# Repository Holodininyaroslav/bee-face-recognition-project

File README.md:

# Bee Face Recognition Project

> **Security update (2026-09-05):** restart/update local installations; replace previously downloaded installers. Read [SECURITY.md](SECURITY.md) for protected APIs, migration instructions and limitations.

Bee Face Recognition Project is an AI-assisted engineering prototype by **Yaroslav Kholodinin**, a student at **Shenkar College, Israel**. Its primary implementation is native face recognition in **C++ and CUDA** using YuNet detection, SFace embeddings, and a project-owned CUDA similarity kernel.

The project combines a local face-recognition pipeline, an AI MIPS Hive interface, bee / board / mechanics simulations, partial SystemVerilog AI MIPS hardware sources, and several research-concept modules for future swarm communication.

It is not a commercial production service. It is a portfolio and course-style system integration project: the value is in connecting neural inference, GPU/CPU execution, local simulation tools, hardware-oriented MIPS work, browser UI, installers, and a safer browser-to-local-app bridge into one demonstrable environment.

## Live Links

- GitHub Pages portal:  
  https://holodininyaroslav.github.io/bee-face-recognition-project/
- Repository:  
  https://github.com/Holodininyaroslav/bee-face-recognition-project
- Full local suite installer:  
  https://github.com/Holodininyaroslav/bee-face-recognition-project/releases/latest/download/bee_face_full_local_suite_installer.zip
- Optional Colab notebook:  
  https://colab.research.google.com/github/Holodininyaroslav/bee-face-recognition-project/blob/main/colab/colab_public_one_image_site.ipynb
- Native CUDA face-recognition source:
  https://github.com/Holodininyaroslav/bee-face-recognition-project/tree/main/source/native_face_cuda

## Primary Native C++ / CUDA Implementation

Face recognition is the main CUDA workflow in this repository. The native worker decodes and prepares an image in C++, detects and aligns the face with YuNet, generates a 128-dimensional SFace embedding through the CUDA execution path, and compares it with stored reference embeddings using the explicit `sface_cuda.cu` kernel. A sequential native CPU path provides the correctness and performance baseline.

The GitHub Pages portal presents this recognition pipeline first and exposes its exact active C++/CUDA source in seven inspectable stages. The surrounding Hive, bee-simulation, hardware, and communication modules remain integrations around this central recognition engine.

## What Works Now

The current project package is built around the local Hive service.

- Local face recognition through the Hive service.
- Local CPU recognition path.
- Local OpenCL recognition path for AMD/Radeon-style systems.
- Optional Colab/CUDA detector path for an external notebook session.
- Integrated AI MIPS Hive interface with processor hexes, detections, events, and local tool launch buttons.
- Bee/statue 3D swarm simulation where bee processors can capture a face view and send it to the detector.
- Automatic detection logging in the Hive detection stream.
- BeeBoard 3D review with GLB / STEP / KiCad assets.
- Physical wing calibration / bee-shell simulation.
- Browser CAD mechanics simulation.
- Bgame linked 2D/3D game demonstration.
- Separate NVIDIA/CUDA local bee-game implementation with GPU face matching.
- Local installer package for the complete tool suite.

## NVIDIA/CUDA Local Bee Game

The repository includes an NVIDIA simulation package at
`installers/nvidia_bee_simulation/`. It contains the local 2D/3D bee game,
mini-map, three face statues, model assets, and a native C++ face-recognition
worker. The CUDA worker uses ONNX Runtime CUDAExecutionProvider for YuNet and
SFace and the project-owned `sface_cuda.cu` kernel for identity scores. It
refuses to report CUDA success when the CUDA provider is unavailable.

The existing AMD/OpenCL detector, CPU path, and original local game package
remain unchanged. See the NVIDIA folder README for installation and launch
instructions.

## Face Recognition Pipeline

The face detector is intentionally exposed as an engineering pipeline instead of a hidden black box.

The GitHub Pages simple demonstration accepts exactly one screenshot. Its
six-stage source inspector loads 434 exact lines from
`source/native_face_cuda/src/sface_engine.cpp` and
`source/native_face_cuda/src/sface_cuda.cu`. Every displayed line has a
line-specific explanation in English, Russian, and Hebrew. The page checks the
loaded source-block line count before displaying it. Batch controls and the
50/500 simulation paths are not part of this one-screenshot demonstration.

1. **Image capture** - the Hive UI, simple demo, or bee simulation provides an image / screenshot.
2. **Native C++ image preparation** - C++ decodes PNG/JPEG, resizes, pads, and packs the YuNet input into NCHW BGR floats.
3. **CUDA face detection** - ONNX Runtime executes the YuNet graph through CUDAExecutionProvider; C++ decodes its boxes, confidence, and five landmarks.
4. **Native C++ alignment and CUDA embedding** - C++ computes the five-landmark similarity transform and bilinear crop; ONNX Runtime executes the SFace graph through CUDAExecutionProvider.
5. **Explicit CUDA reference comparison** - `sface_cuda.cu`, compiled by NVCC, assigns one CUDA thread to each query/reference cosine score and returns the score matrix.
6. **One JSON response** - only the final small scores and indices return to the host; Hive receives one label, score, runner-up, margin, provider, timing, and accepted/rejected state.
7. **Hive event logging** - the result is written into the Hive detection stream.

## Local Detector Modes

The installer includes the local detector pieces required for a fresh machine:

- native `identity_cpu.exe` and `identity_cuda.exe` workers
- local reference embeddings and face reference images
- optional OpenCL detector executable for the legacy AMD path
- CPU detector executable
- neural model weights
- Hive server routes for `/api/detect` and `/api/detector-status`

Recommended behavior:

- **AMD/Radeon machine:** use the optional OpenCL path.
- **No supported GPU:** use the CPU path.
- **NVIDIA/CUDA machine:** use the local ONNX Runtime CUDA YuNet/SFace pipeline installed with the NVIDIA suite.

For the local NVIDIA game implementation, use
`installers/nvidia_bee_simulation/Start NVIDIA Bee Simulation.bat` after the
native CUDA worker and ONNX Runtime CUDA dependencies have been installed.

Colab is no longer the only path. It is an optional external GPU service and must be connected deliberately.

## AI MIPS Hardware Layer

The repository includes partial SystemVerilog hardware sources for the AI MIPS processor / accelerator concept:

```text
hardware/ai-mips-rtl/
```

This folder includes processor modules, datapath/control files, memory blocks, ALU logic, matrix / ReLU accelerator helpers, Quartus project files, and simulation testbenches.

This matters because the project is not only a web UI. It also keeps hardware-oriented work that represents the planned compute layer for bee nodes.

## System Architecture

```mermaid
flowchart LR
    Site["GitHub Pages portal"] --> Simple["Simple recognition demo"]
    Site --> HiveView["Integrated Hive interface"]
    Simple --> DetectorChoice["Detector mode selection"]
    HiveView --> LocalSuite["Approved local suite"]
    DetectorChoice --> LocalDetector["Local CPU / OpenCL detector"]
    DetectorChoice --> Colab["Optional Colab / CUDA detector"]
    LocalSuite --> LocalDetector
    LocalSuite --> Bee3D["Bee/statue swarm simulation"]
    LocalSuite --> Board["BeeBoard 3D review"]
    LocalSuite --> Physical["Physical wing simulation"]
    LocalSuite --> CAD["Browser CAD mechanics"]
    LocalSuite --> Game["Bgame 2D/3D demo"]
    LocalSuite --> Network["Network concepts"]
    Network --> Lifi["Li-Fi concept"]
    Network --> EOS["EOS smart-contract sandbox"]
    Network --> Satellite["Satellite/orbital concept"]
    LocalDetector --> Log["Hive detections and timing log"]
```

## Working vs Concept Modules

| Module | Current status |
|---|---|
| Local face recognition | Working local software path through Hive |
| CPU detector | Working local fallback |
| OpenCL detector | Working local GPU path for AMD/Radeon-style systems |
| Colab/CUDA detector | Optional external runtime; URL changes per Colab session |
| AI MIPS Hive interface | Working local/web UI prototype |
| Bee/statue swarm simulation | Working local simulation |
| BeeBoard 3D review | Working local package with model assets |
| Physical wing simulation | Working local simulation package |
| Browser CAD mechanics | Working local browser simulation |
| Bgame | Working local linked 2D/3D game package |
| AI MIPS RTL | Partial hardware source / educational prototype |
| Li-Fi | Physical hardware prototype exists; software module is a project concept layer |
| Quadcopter bee proxy | Physical prototype exists as a bee-like hardware platform |
| Satellite communication | Concept / local orbital simulation only |
| EOS blockchain | Local sandbox / concept smart contract; not live mainnet infrastructure |
| Bioreactor / plastic-to-energy | Future concept stage |

## Install on Another Computer

Use the full suite package first:

```text
bee_face_full_local_suite_installer.zip
```

It installs the local Hive service, the native C++ CPU baseline, the native
C++/CUDA worker with the project-owned manual SFace kernels, model weights,
reference images, BeeBoard assets, Bgame, physical/mechanics tools, concept
pages, and launch scripts as one synchronized package.

After extraction, run `Install_Hive.bat`. The installer validates every payload
file, creates an isolated Python environment, tests CPU recognition, tests the
`manual-cuda-sface` backend on NVIDIA systems, checks the Hive API, and creates
the desktop/startup shortcuts. The stable local address is
`http://127.0.0.1:8890/`.

Detailed steps:

```text
CODEX_OTHER_PC_INSTALL.md
```

The individual component ZIP files are kept as recovery assets, but the normal workflow should use the full suite installer.

## Local Bridge Security

The public GitHub Pages site does not automatically control local applications.

The local bridge is designed around:

- localhost-only services;
- explicit user approval;
- per-action allowlists;
- a private local token;
- no silent reconnection after long idle periods.

The goal is to let the public site open approved local tools without making the computer remotely controllable by random visitors.

Security notes:

```text
SECURITY_LOCAL_BRIDGE.md
```

## Communication and Blockchain Concepts

These are included as research extensions, not as finished production systems.

- **Li-Fi communication** is the nearest hardware-related communication direction. The project has physical Li-Fi work/prototype context, and the software branch is used to document and expand the swarm-network idea.
- **Satellite communication** is a local simulator for satellite orbits.
- **EOS smart contract sandbox** simulates a treasury, node registry, job ledger, result ledger, and installer hash registry. It is a local educational smart-contract concept, not a live blockchain deployment.

## Roadmap

Near-term:

- tighten the local detector installer and tests;
- add a clearer mechanical flight map;
- improve local GPU packaging for additional hardware;
- expand the AI MIPS RTL documentation;
- connect Hive events more cleanly to simulation modules.

Long-term:

- distributed bee datacenter simulation using many AI MIPS nodes;
- Li-Fi swarm networking between nearby bee nodes;
- nano-capacitor energy storage simulation;
- deeper bee mechanical model;
- bioreactor / plastic-to-energy concept simulation;
- future blockchain-backed registry for nodes, jobs, and package integrity.

## Repository Layout

```text
/
|-- index.html
|-- script.js
|-- styles.css
|-- assets/
|-- colab/
|-- database/
|-- hardware/
|   `-- ai-mips-rtl/
|-- installers/
|-- source/
|-- CODEX_OTHER_PC_INSTALL.md
|-- SECURITY_LOCAL_BRIDGE.md
`-- README.md
```

## AI-Assisted Development Note

This project was built with AI-assisted development. The engineering work includes project direction, system integration, testing, UI iteration, detector workflow, packaging decisions, hardware/software organization, and safety constraints. AI assistance is part of the workflow, not a claim that the project appeared without engineering decisions.

## Resume Summary

**Bee Face Recognition Project** - AI-assisted engineering prototype by Yaroslav Kholodinin integrating local CPU/OpenCL face recognition, optional Colab/CUDA inference, an AI MIPS Hive interface, bee/statue 3D simulation, BeeBoard 3D review, physical and CAD mechanics simulations, partial SystemVerilog AI MIPS hardware sources, local installers, and research-concept modules for Li-Fi, satellite, and EOS-based swarm infrastructure.

## Final Satellite And BeeBoard Packages

The repository contains the final source trees and self-contained installers used by the current local project:

- [BeeBoard interface source](source/beeboard/BeeBoard_Interface/)
- [BeeBoard 3D model and CAD assets](source/beeboard/BeeBoard_v0_1_Micro_KiCad/)
- [BeeBoard installer](installers/beeboard_interface_installer.zip)
- [Satellite Communication source and Three.js assets](source/satellite/Satellite_Communication/)
- [Satellite Communication installer](installers/satellite_communication_installer.zip)

BeeBoard's 3D Board Review loads `source/beeboard/BeeBoard_v0_1_Micro_KiCad/BeeBoard_v0_1_Micro.glb` from the package-local `BeeBoard_v0_1_Micro_KiCad` directory. The package also includes the KiCad, STEP, SVG, SCAD, and preview assets used by the board-design view.

Run `source/beeboard/BeeBoard_Interface/install_and_run.bat` on Windows to create its virtual environment and start BeeBoard at `http://127.0.0.1:8877/`.
Run `source/satellite/Satellite_Communication/Start Satellite Communication.cmd` to start the local satellite simulator at `http://127.0.0.1:8765/`.

Both installers are built from the same source directories linked above, so the archive and source tree stay aligned.

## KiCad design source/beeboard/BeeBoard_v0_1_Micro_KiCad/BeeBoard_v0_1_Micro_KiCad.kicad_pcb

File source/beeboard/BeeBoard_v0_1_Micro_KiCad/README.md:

# BeeBoard v0.1 Micro KiCad

This is the aggressive compact KiCad revision of BeeBoard v0.1.

- Board size: 20 mm x 12 mm.
- Stackup: 4 copper layers, 0.6 mm target PCB thickness.
- FPGA / future BeeSoC contains the AI MIPS, MatrixAccel, ReLU blocks, crypto,
  power control, motion control, LiFi controller, sensor interface and memory
  controller.
- External parts are kept only where physics forces them off-chip: power
  harvesting/storage, configuration Flash, IMU, optical LiFi devices, low-voltage
  actuator drivers, and flex/castellated edge pads.

The file is a compact layout draft for architecture and mechanical iteration.
It is not a fabrication-ready Gerber package yet.

See `BeeBoard_v0_1_Micro_Explanation_RU.md` for the Russian block/layer
explanation, and use `BeeBoard_v0_1_Micro.glb`,
`BeeBoard_v0_1_Micro_board_layers.step`, and
`BeeBoard_v0_1_Micro_Layered3D.scad` for 3D review.

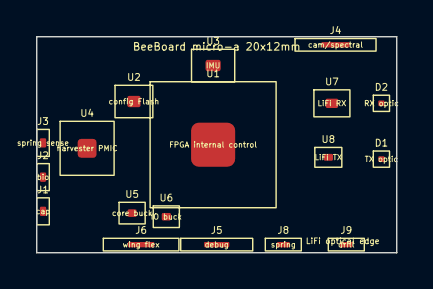
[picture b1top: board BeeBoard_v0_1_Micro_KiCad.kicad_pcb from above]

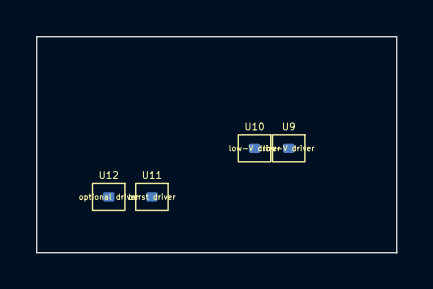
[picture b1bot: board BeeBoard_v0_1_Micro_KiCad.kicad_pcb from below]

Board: 4 copper layers, 20.0 x 12.0 mm, 22 parts (4 on the bottom side), 6 nets, no tracks yet.

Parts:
D1: microLED LiFi TX; D1_micro_placeholder
D2: photodiode LiFi RX; D2_micro_placeholder
J1: supercap pads; J1_micro_placeholder
J2: bio input pads; J2_micro_placeholder
J3: spring sense pads; J3_micro_placeholder
J4: camera/spectral flex; J4_micro_placeholder
J5: debug test pads; J5_micro_placeholder
J6: wing flex pads; J6_micro_placeholder
J8: spring release pads; J8_micro_placeholder
J9: drill/cutter pads; J9_micro_placeholder
U1: iCE40UP5K-SG48 / BeeSoC proto; U1_micro_placeholder
U2: W25Q32JV WSON; U2_micro_placeholder
U3: BMI270 LGA; U3_micro_placeholder
U4: BQ25570/LTC3108 opt; U4_micro_placeholder
U5: TPS62740 1V2; U5_micro_placeholder
U6: TPS62840 3V3; U6_micro_placeholder
U7: fast TIA / comparator; U7_micro_placeholder
U8: low-side LED switch; U8_micro_placeholder
U9: DRV8838 wing A; U9_micro_placeholder
U10: DRV8838 wing B; U10_micro_placeholder
U11: DRV8838 spring; U11_micro_placeholder
U12: DRV8838 drill; U12_micro_placeholder

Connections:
ACT_DRILL: J9.1, U12.1
ACT_SPRING: J8.1, U11.1
ACT_WING_A: J6.1, U9.1
LIFI_RX: D2.1, U7.1
LIFI_TX: D1.1, U8.1
SUPERCAP_RAW: J1.1, U4.1

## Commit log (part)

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2026-06-12 Publish Bee Face recognition project
2026-06-12 Open local BeeBoard directly
2026-06-12 Fix Pages project routing and backup site
2026-06-12 Direct simple demo and split simulator hex actions
2026-06-12 Refresh live Colab service URL
2026-06-12 Fix Pages demo and local simulator links
2026-06-12 Explain detector pipeline in simple demo
2026-06-12 Add detector stage architecture diagrams
2026-06-12 Add localized diagram node explanations
2026-06-12 Document CUDA commands per detector stage
2026-06-12 Fix physical simulation wing calibration route
2026-06-12 Disable public Colab share by default
2026-06-12 Disable public bridge links for safety
2026-06-12 Rename identity engine references
2026-06-13 Make Colab engine lookup robust
2026-06-13 Enable safe local project bridge
2026-06-13 Label local Hive detector mode
2026-06-13 Annotate CUDA code explanations by language
2026-06-13 Add full Colab CUDA code annotations
2026-06-13 Add full detector source viewer
2026-06-13 Harden local bridge access
2026-06-14 Attach current bee-shell physical simulator installer
2026-06-14 Hide local bridge token after approved load
2026-06-14 Document Bee Face Recognition project
2026-06-14 Describe distributed bee datacenter concept
2026-06-15 Add project avatar and idle bridge approval
2026-06-15 Normalize Bee Face Recognition title
2026-06-15 Simplify local bridge reconnect flow
2026-06-15 Use browser confirm for local bridge approval
2026-06-15 Move local bridge approval to browser prompts
2026-06-15 Update roadmap and bridge security docs
2026-06-15 Allow approved local portal bridge
2026-06-15 Redirect public complex view to local portal
2026-06-15 Use approved online local bridge session
2026-06-15 Keep approved local bridge session active
2026-06-17 Point Ursina installer to final release asset
2026-06-19 Run complex demo from GitHub Pages
2026-06-19 Restore original Hive complex interface
2026-06-19 Bust cached Pages script
2026-06-19 Fix local bridge install and launch flow
2026-06-19 Restore local bridge idle timer
2026-06-19 Allow public page to request local approval
2026-06-19 Open approved complex view in local portal
2026-06-20 Rename Ursina entry to game demonstration
2026-06-20 Label Bgame installer on project site
2026-06-20 Point Bgame launch to local Bgame route
2026-06-20 Point Bgame download to release asset
2026-06-23 Refresh installer links and physical package
2026-06-23 Add setup guide for another computer
2026-06-23 Clarify fresh computer install guide
2026-06-23 Add AI MIPS Hive Service installer link
2026-06-29 Document BeeBoard 3D model installer contents
2026-06-29 Document mechanic simulation in Hive installer
2026-06-30 Add EOS blockchain simulation docs
2026-06-30 Document packaged CAD mechanics simulator
2026-06-30 Document communication concepts and installers
2026-06-30 Add satellite communication installer docs
2026-06-30 Use full local suite installer
